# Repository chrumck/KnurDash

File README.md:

# KnurDash - Racing Data Logger with [RaceChrono](https://racechrono.com/) Integration

## Description

A racing logger for an ND2 Mazda MX-5, integrating wide ranging functionality into one unit:

- Reading analog sensors (oil pressure and temperature, rotor temperature)
- Reading CANBUS data (coolant and intake temperature, RPM, etc.)
- Displaying data in a clear and aesthetically pleasing way
- Making data available via Bluetooth as [RaceChrono DIY BLE device](https://github.com/aollin/racechrono-ble-diy-device)

---

## Technical Details

The system has two main components, the display unit and the sensor unit. The communication between the two is executed through I2C protocol (1.2m cable is pushing it though. With careful cable prep I still get ~0.5% error rate on comms.). The display unit is made of a Raspberry Pi 4B board and a [4.3 inch touchscreen](https://www.waveshare.com/4.3inch-dsi-lcd-with-case.htm). The sensor unit houses a [5V power supply](https://www.pololu.com/product/3782/specs), two [4-channel ADC's](https://www.dfrobot.com/index.php?route=product/product&product_id=1182&search=DFR0316), a [motion tracking device](https://www.dfrobot.com/index.php?route=product/product&product_id=880), and a [Longan Labs I2C CAN Controller](https://docs.longan-labs.cc/1030017/) with a [custom firmware](https://github.com/chrumck/I2C_CAN_Firmware) built specifically for this project.

Additionally, the sensor unit contains circuitry [(LTSpice schematic)](./LTSpice/PowerOffCircuit.asc) allowing starting the system when the vehicle's START button is pressed. This has been accomplished by pulling RPI's GLOBAL_EN to ground when RPI is off. When RPI is running and [3.3V is on](https://www.raspberrypi.com/documentation/computers/raspberry-pi.html#POWER_OFF_ON_HALT), the starting circuit is disabled to prevent hard resets while RPI system and the OS is running.

Bluetooth communication was implemented using the [bluez_inc](https://github.com/weliem/bluez_inc) library (kudos to [weliem](https://github.com/weliem) for making my life easier!). The system implements the [RaceChrono BLE DIY](https://github.com/aollin/racechrono-ble-diy-device) protocol. The system works as a pass-through for selected CAN frames. Additionally, all analog data collected by the unit is exposed as an additional CAN frame and made available to RaceChrono for logging.

The display unit has a buzzer installed. The buzzer is turned on when the oil pressure drops below a certain threshold and the RPM is above idling.

The rotor temperature is measured with an industrial grade 0~1000 degC infrared pyrometer with a 4-20mA output.

As of 2023-09-04, the system is installed in the car and in initial testing . The transmission, differential, and rotor temperature sensors were not installed yet, but coming soon!

Future development:

- Read motion tracking data from the already installed unit and expose it to RaceChrono
- Add a [differential GPS](https://www.sparkfun.com/products/15136) board

---

## Pictures

### Display Unit

### Sensor Unit

### Sensors

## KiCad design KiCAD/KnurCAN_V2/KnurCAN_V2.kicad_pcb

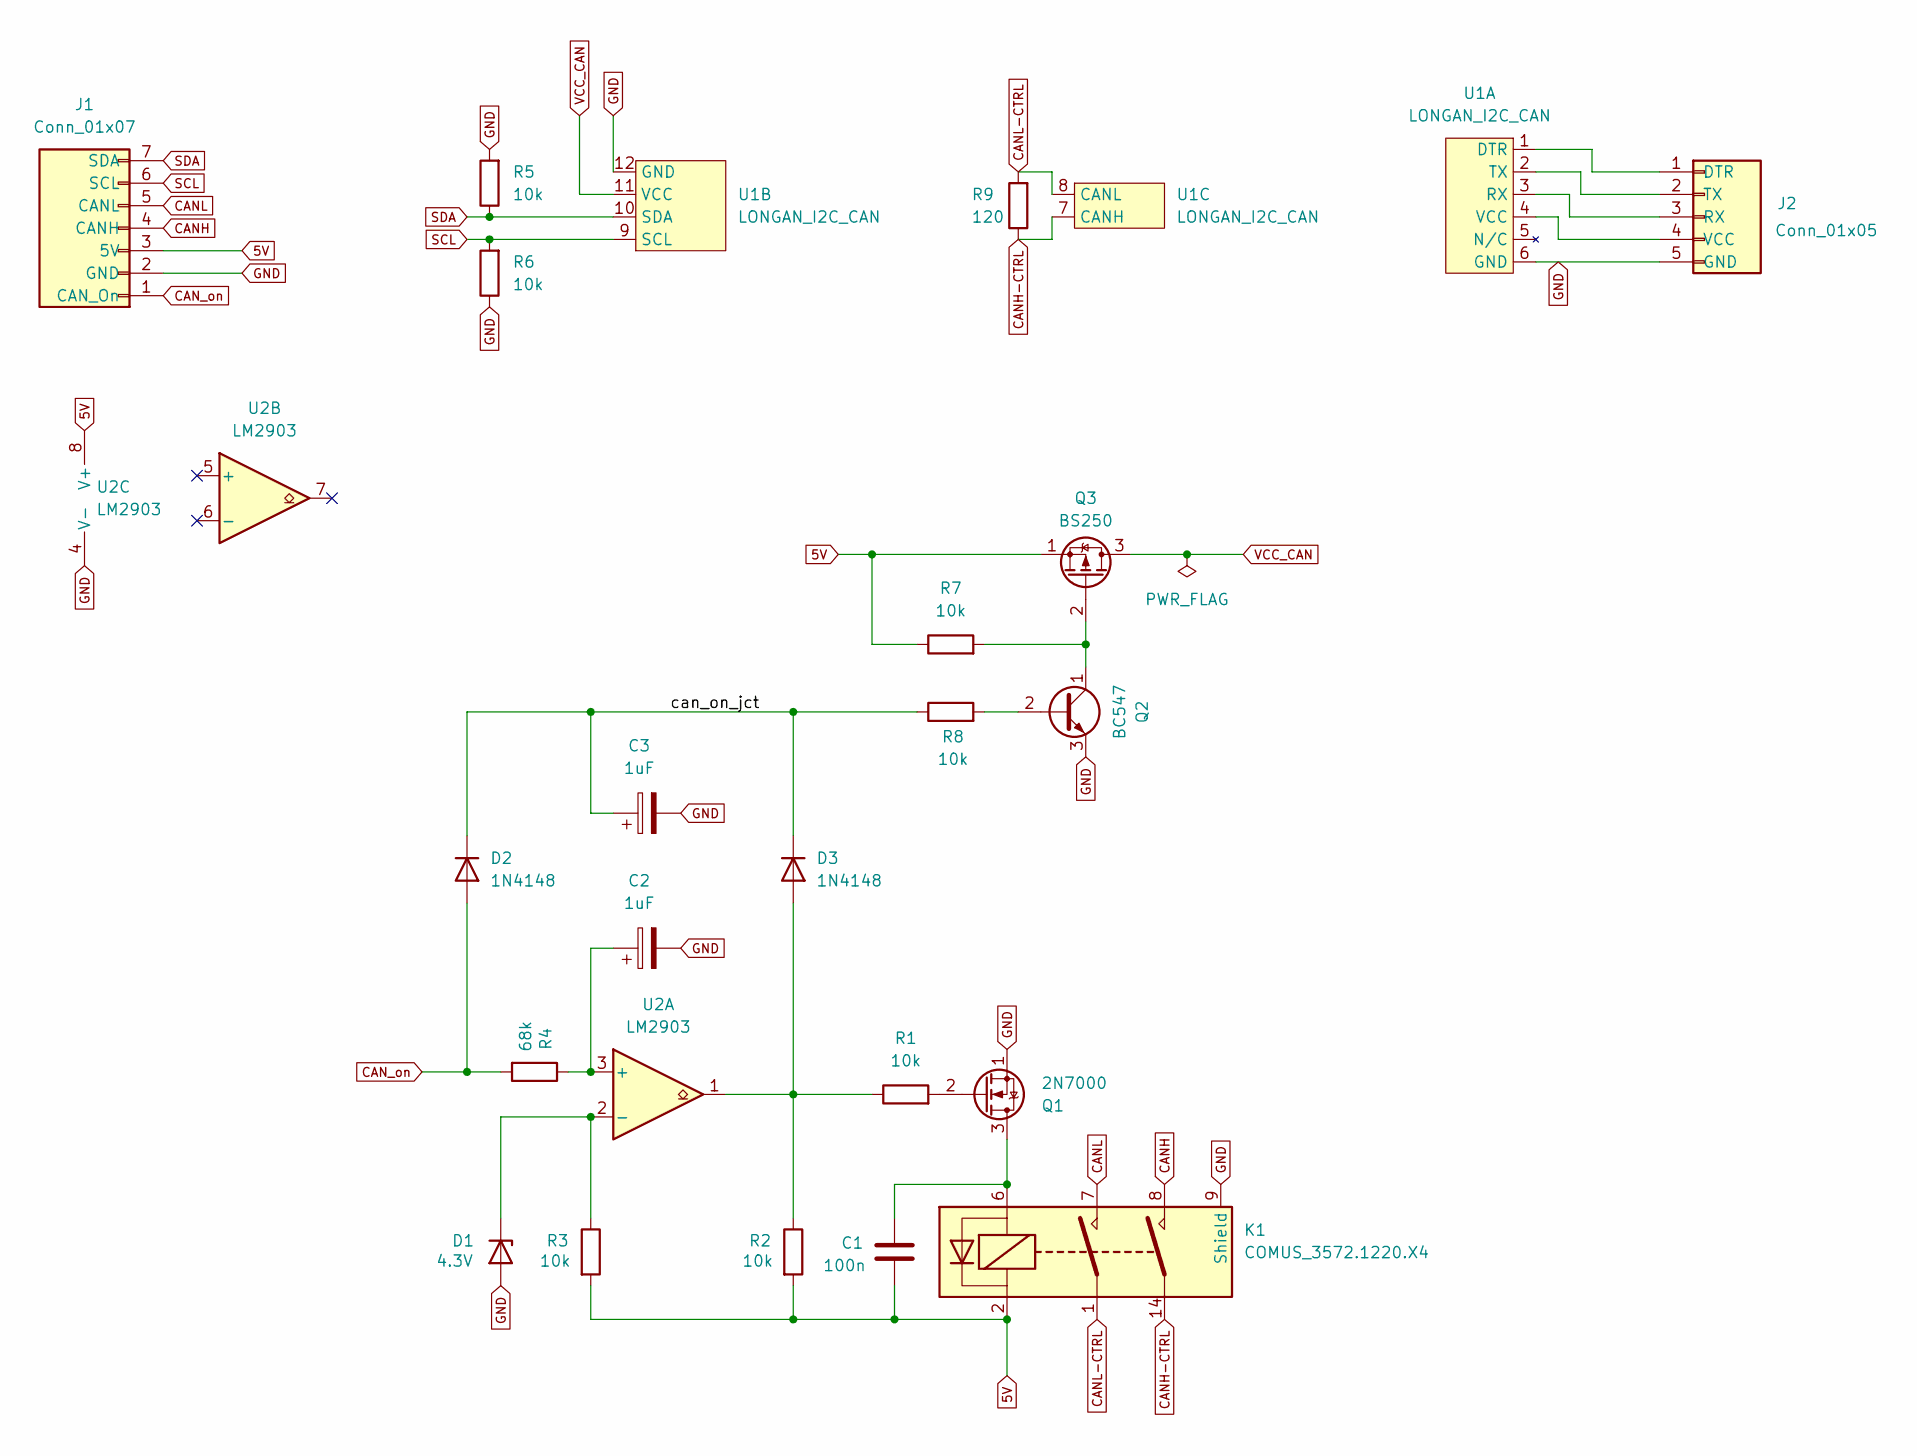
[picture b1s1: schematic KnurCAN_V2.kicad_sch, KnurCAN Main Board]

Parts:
C1: 100n; C_Disc_D3.8mm_W2.6mm_P2.50mm
C2, C3: 1uF; CP_Radial_D5.0mm_P2.50mm
D1: 4.3V; D_DO-35_SOD27_P7.62mm_Horizontal
D2, D3: 1N4148; D_DO-35_SOD27_P7.62mm_Horizontal
J1: Conn_01x07; SolderWire-1x07-d1.5
J2: Conn_01x05; PinHeader_1x05_P2.54mm_Vertical
K1: COMUS_3572.1220.X4; Relay_COMUS_DIP
Q1: 2N7000; TO-92_Inline_Wide
Q2: BC547; TO-92_Inline_Wide
Q3: BS250; TO-92_Inline_Wide
R1, R2, R3, R5, R6, R7, R8: 10k; R_Axial_DIN0207_L6.3mm_D2.5mm_P7.62mm_Horizontal
R4: 68k; R_Axial_DIN0207_L6.3mm_D2.5mm_P7.62mm_Horizontal
R9: 120; R_Axial_DIN0207_L6.3mm_D2.5mm_P7.62mm_Horizontal
U1: LONGAN_I2C_CAN; Longan_I2C_CAN
U2: LM2903; DIP-8_W7.62mm

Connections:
5V: C1.2, J1.3 (5V), K1.2, Q3.1 (S), R2.2, R3.2, R7.1, U2.8 (V+)
/can_on_jct: C3.1, D2.1 (K), D3.1 (K), R8.1
CANH: J1.4 (CANH), K1.8
CANH-CTRL: K1.14, R9.1, U1.7 (CANH)
CANL: J1.5 (CANL), K1.7
CANL-CTRL: K1.1, R9.2, U1.8 (CANL)
CAN_on: D2.2 (A), J1.1 (CAN_On), R4.2
GND: C2.2, C3.2, D1.2 (A), J1.2 (GND), J2.5 (GND), K1.9 (Shield), Q1.1 (S), Q2.3 (E), R5.2, R6.1, U1.6 (GND), U1.12 (GND), U2.4 (V-)
unnamed: D1.1 (K), R3.1, U2.2 (-)
unnamed: D3.2 (A), R1.1, R2.1, U2.1
unnamed: J2.1 (DTR), U1.1 (DTR)
unnamed: J2.3 (RX), U1.3 (RX)
unnamed: J2.2 (TX), U1.2 (TX)
unnamed: J2.4 (VCC), U1.4 (VCC)
unnamed: C1.1, K1.6, Q1.3 (D)
unnamed: Q1.2 (G), R1.2
unnamed: Q2.2 (B), R8.2
unnamed: Q2.1 (C), Q3.2 (G), R7.2
unnamed: C2.1, R4.1, U2.3 (+)
SCL: J1.6 (SCL), R6.2, U1.9 (SCL)
SDA: J1.7 (SDA), R5.1, U1.10 (SDA)
VCC_CAN: Q3.3 (D), U1.11 (VCC)

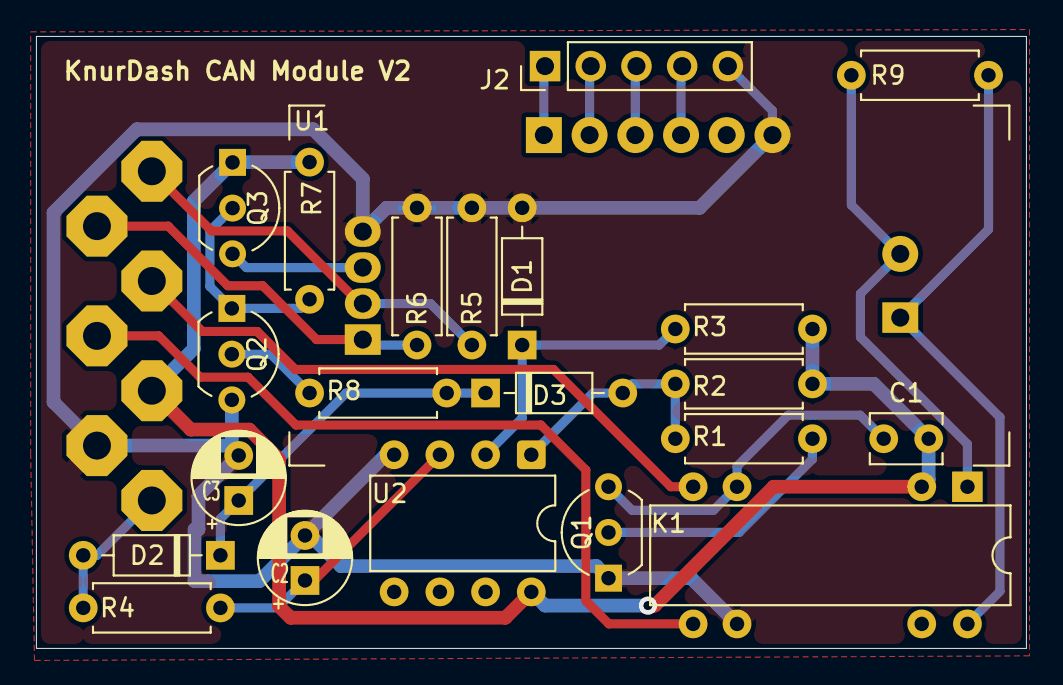
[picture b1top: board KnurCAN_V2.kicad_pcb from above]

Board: 2 copper layers, 55.0 x 34.0 mm, 23 parts (0 on the bottom side), 22 nets.

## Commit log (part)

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2023-05-14 Add gtk3
2023-05-14 Update gitignore
2023-05-14 Clean up CMakeLists, add main.ui
2023-05-14 Minor updates
2023-05-14 More fixes
2023-05-15 Tinkering with main.ui parsing
2023-05-15 Added TURN OFF button
2023-05-15 Fix uiFileName weird bug - strange characters
2023-05-15 Add width and height to KnurDash.ui
2023-05-15 Remove compiled files
2023-05-15 Set decorate false and go fullscreen
2023-05-16 Add CSS, finish ui work
2023-05-17 Add setBrightness
2023-05-19 remove Print_hello
2023-05-19 Put brightness logic in separate file
2023-05-19 Add sensors.c
2023-05-19 trying to fix language mode incompatible
2023-05-20 First try to add pigpio
2023-05-20 second attempt to link pigpio
2023-05-20 Refactor shutDown to gracefully stop workers
2023-05-20 Add buttonShutDown and windowShutDown
2023-05-20 Change code to use pigpiod deamon
2023-05-20 Move shutdown callbacks to ui.c
2023-05-20 Add i2cOpen
2023-05-20 2st try to read from adc
2023-05-20 Change to i2c_read_device; maybe fix cmake extension problems
2023-05-20 Getting first readings from channel 1
2023-05-20 Minor cleanup and progress
2023-05-21 Clean up filepath stuff
2023-05-21 minor fix
2023-05-21 Add deadband
2023-05-21 Finish reading oil channel, I wonder if it works
2023-05-22 Refactor ReadChannelArgs into ChannelProps
2023-05-22 Refactor sensors.c to take new SensorProps
2023-05-22 Start working on populating min/max values
2023-05-23 Renames and cleanup
2023-05-23 More minor fixes and cleanup
2023-05-23 Add resetting min and max. Other refactor and cleanup
2023-05-23 Fix memory leak around SetLabelArgs
2023-05-23 convert some macros to functions
2023-05-24 Fix bug with min max labels not available for min max reset; Cleanup and refactor
2023-05-24 Add precision and deadband logic
2023-05-24 Add testing limits and handling css classes
2023-05-24 Minor tweak to css
2023-05-24 Add FAULTY_READING_VALUE
2023-05-24 Minor fix in resetLastReadings
2023-05-25 Add VDD sensor reading and consume it for other sensors
2023-05-25 update compile files
2023-05-28 Add reading ignition state and shutdown on ignition off
2023-05-28 Build release
2023-05-29 Add design files and photos
2023-05-29 update xls
2023-05-30 update pics
2023-06-03 Tweak sensor props
2023-06-03 update build files
2023-06-11 Minor cleanup
2023-06-11 Minor refactor
2023-06-11 Add handling of unix signals
2023-06-11 Minor update
2023-06-11 Add boot folder
2023-06-12 Add bluez_inc
2023-06-12 Reconfigure CMakeLists to include Binc
2023-06-15 Add bluetoothWorker.c
2023-06-16 Add attempt to power back up if bt adapter not powered
2023-06-16 Progressing work on bt worker
2023-06-16 Continuing work with bt worker
2023-06-17 Add CAN decoding xls
2023-06-18 Finished BT worker shutdown logic
2023-06-18 disable app shutdown on engine off when debugging
2023-07-11 Add dbc for SavvyCAN
2023-07-11 Update x202 frame defs
2023-07-11 More work on DBC
2023-07-11 xlsx update
2023-07-12 Update log messages and shutdown logic
2023-07-12 update knurdash.service with TimeoutStopSec=5
2023-07-12 Move initializing pigpiod pi handle to main.c
2023-07-12 Add CanBusData DTO
2023-07-13 Add canBusWorker
2023-07-13 update write result check
2023-07-13 Add mask and filter setting
2023-07-13 Add can filter/mask messaging and delay in setting
2023-07-14 Add 3 more frame ids
2023-07-15 Add early return to CAN setMaskOrFilter
2023-07-15 Add canBusProps file; move constants there; start working on storing can frames
2023-07-15 Move worker data to a global variable
2023-07-15 Fix bt worker not shutting down properly
2023-07-15 Start adding canbus worker loops
2023-07-15 change isSent to isReady
2023-07-15 add sensors frame id
2023-07-16 Rename to KNURDASH_FRAME_ID
2023-07-16 Add workerData.c to canBusWorker
2023-07-16 add getFrameFromCAN
2023-07-16 Add getRpm
2023-07-16 Add buzzer handling to sensorWorker
2023-07-16 minor fixes
2023-07-17 Add IS_DEBUG
2023-07-17 leave buzzer logic on when debugging
2023-07-17 update CAN errors reporting
2023-07-17 fix bug in setMaskOrFilter - delete extra return;
2023-07-17 Make canbus statistics be reported at shutdown
2023-07-18 minor messages formatting
2023-07-18 Refactor gauges to consolidate min/max with main label
2023-07-18 Update css to match the new UI
2023-07-18 Rename windowShutdown to appShutdown
2023-07-18 refactor shutDown to accept ShutdownType enum as pointer
2023-07-18 minor rename
2023-07-19 Refactor sensor DTO to separate base properties
2023-07-19 Add CanSensor DTO and definition for coolant temp
2023-07-19 Add coolant temp can sensor to sensorWorker
2023-07-19 Add request rejected check in setMaskOfFilter
2023-07-19 decrease can buss polling to ~20Hz
2023-07-19 update error messages
2023-07-19 update temp sensors min/max values
2023-07-19 bump OIL_PRESSURE_ALERT_MIN_RPM
2023-07-19 minor cleanup in ui
2023-07-19 add ENABLE_CAN_READ_ERROR_LOGGING
2023-07-20 Add btWasSent reset to getFrameFromCAN
2023-07-20 move bt advertisement to workerData
2023-07-20 wire up onCharStartNotify and onCharStopNotify
2023-07-20 Set BT error messages
2023-07-22 add reading locking on reading update; clean up reading sensor logic
2023-07-22 start adding getAdcFrame
2023-07-22 add racechrono to workspace dict
2023-07-22 finish implementation of getAdcFrame
2023-07-22 fix typo in getAdcFrame
2023-07-22 add sensor reading locking in resetReadingsValues
2023-07-22 read adc sensors in reverse order
2023-07-22 fix getAdc frame passing
2023-07-23 make sensorWorker set adc can frame
2023-07-23 move CAN_FRAME_ID_LENGTH to dataContracts
2023-07-23 lock adc can frame before setting default values
2023-07-23 implement onCharRead
2023-07-23 rename sensorData to sensors
2023-07-23 rename canBusData to canBus
2023-07-23 rename bluetoothData to bluetooth
2023-07-23 Start implementing onCharWrite
2023-07-23 add early return on requestShutdown in getFrameFromCAN
2023-07-23 add sendCanFrameToBt, continue with onCharWrite
2023-07-23 finish implementation onCharWrite
2023-07-23 update bt logging
2023-07-23 fix bug aroung byte array sizing
2023-07-23 round temps to nearest degree before creating adc can frame
2023-07-23 increase data acquisition speed
2023-07-23 tweak bt and canbus shutdown logic
2023-07-24 make sure the min,max are repopulated after clearing
2023-07-24 add error rate tracking to sensor readings
2023-07-24 Add bluetooth.isConnected and removing sources on disconnecting
2023-07-24 Add app shutdown on excessive canbus error rate
2023-07-24 fix bug in getting connection state name
2023-07-24 fix source removing logic in bluetooth worker
2023-07-24 switch to release version
2023-07-24 remove bluetooth.isConnected
2023-07-24 set bt worker log level to info at all times
2023-07-24 add disconnecting info on shutdown
2023-07-25 update dbc
2023-07-25 fix pressure rounding bug
2023-07-25 clean up buzzer on/off logic
2023-08-29 update dbc file
2023-08-29 canbus decoding updates
2023-08-30 working on CAN decoding
2023-08-31 Add rotor temp sensor definition
2023-08-31 updates to sensor calcs
2023-09-02 Update pinouts
2023-09-02 add adcConfig to AdcSensor definition
2023-09-02 Add rotor temp reading step to sensor worker; change temp offset to 40degC
2023-09-02 Change MAX_REQUEST_ERROR_RATE to 0.20
2023-09-02 Add rotor temp to ui
2023-09-02 Fix rotor temp calcs
2023-09-03 Add startup retry logic to canBusWorker
2023-09-03 add 5 second delay to shutting down due to errors
2023-09-04 update bluez_inc to latest master
2023-09-04 Update photos and add README
2023-09-04 Add license
2023-09-10 can decoding updates
2023-09-10 update coolant temp rawMin and rawMax
2023-09-10 add delay between canbus start retries
2023-09-10 bump pressure precision to 0.05 bar
2023-09-11 add diff and trans temp frames to ui
2023-09-11 update wiring file
2023-09-12 add fault tolerance of 5 faults to sensorworker
2023-09-12 allow more sensor worker logging when error count > 5
2023-09-13 Add more shutdown scenarios
2023-09-13 change canbus frame state from receiveFailed to errorCount
2023-09-13 add repeat reading of mask/filter after setting it.
2023-09-13 improve sensor worker shutdown logic when CAN coolant temp reading in error
2023-09-13 Improve messaging for CAN initialization
2023-09-13 Do not increment sensors.errorCount on repeat out of range readings
2023-09-14 Add checksum to mask/filter setting
2023-09-14 fix mask/filter getting logic - request to get and response too fast
2023-09-14 tweak shutting down on coolant errors
2023-09-14 bump request error rate to 0.5
2023-09-14 minor tweak to shutting down on coolant errors
2023-09-18 add CAN controller switch on/off to canBusWorker
2023-09-18 improve can error handling in sensorWorker
2023-09-19 fix flickering can sensor on ignition off
2023-09-19 Add CAN restart logic without restarting the app
2023-09-19 fix bug in restartCanBus
2023-12-19 Rename WorkerData to AppData
2023-12-19 Add volatile keyword to AppData
2024-02-25 update xls file
2024-02-29 update binc ref to latest main
2024-02-29 remove volatile from appData
2024-02-29 updae build json
2024-03-04 Add ENABLE_CANBUS
2024-03-05 bum CAN I2C request delay to 2ms
2024-03-06 move adc bit resolution to #define
2024-03-06 horten sensorWorker idle time to 25m
2024-03-08 minor refactor and renames
2024-03-08 remove sensorWorker wait on canBusWorker; other minor refactor
2024-03-08 refactor AdcSensor to have pga; no support for adaptive pgs yet; add def for caliper temp
2024-03-08 add support for adaptive pga
2024-03-09 fixes to ui
2024-03-09 fix sensorWorker usage of readAdc
2024-03-09 finish sensor definition for caliper temp
2024-03-09 enable caliper temp reading in sensorWorker
2024-03-09 make canBusWorker abort CAN init on appShutdownRequested
2024-03-09 add config.txt to boot folder
2024-03-09 make sure sensorWorker does not read can sensors if canbus not started
2024-03-09 bump CANBUS startup times
2024-03-09 bump i2c request delay to 3000 us
2024-03-09 revert back to 2ms for canbus i2c request delay
2024-03-10 increase wait time after request for filter, mask
2024-03-10 increase wait time before CAN restart request
2024-03-10 change the way context_iteration is invoked
2024-03-10 change usage of context_iteration in btWorker
2024-03-10 remove pin setting from config.txt
2024-03-10 move can switchoff logic to stopCanBusWorker
2024-03-10 remove i2c_read_byte_data
2024-03-10 lower wait time before restarting canbus from sensorworker
2024-03-10 lower canbus wait times
2024-03-10 update build #
2024-03-10 update build index
2024-03-13 bump lower rotor temp limit to 50 degC
2024-03-13 update build json
2024-03-13 update SensorUnit xls
2024-03-29 tweak rotor temp and oil pressure limits
2024-04-30 updates to SensorUnit; design for trans pump
2024-05-02 Split code from sensorWorker to systemWorker
2024-05-02 Add trans pump switching logic
2024-05-02 Update ui for trans cooling info
2024-05-03 css fixes; add systemWorker to main
2024-05-03 reduce number of status gauges to 2; other ui tweaks
2024-05-03 fix css for status gagues
2024-05-03 add trans pump ui status toggling to system worker
2024-05-03 add sensor worker started message
2024-05-05 change trans pump GPIO to high for ON
2024-05-05 update to CANBUS start, make it wait for sensorWorker
2024-05-05 fix trans pump shutdown at app shutdown
2024-05-05 set trans pump on temp to 95 c
2024-05-05 add isSystemWorkerRunning
2024-07-14 set trans pump off temp to 50 degC
2024-07-23 add app_error; take advantage of pragma once
2024-07-23 adjust temperature limits
2024-07-24 refactor logging and graceful shutdown
2024-07-24 add buzzerToggleTimestamp; more cleanup
2024-07-26 tweak limit values; other refactor
2024-07-26 Add buzzer chirping
2024-07-26 tweak buzzer chirp logic to use cycles instead of us
2024-07-26 minor tweak in chirp logic
2024-07-26 update buzzer logic so it does not run when ign off and rpm below threshold
2025-06-21 Add PCB design for KnurCAN_V2
2025-06-21 update gitignore to exclude kicad backups
2025-08-16 design file updates
2025-08-16 update canBusWorker to work with KnurCan V2
2025-08-16 update bluez_inc to latest main
2025-09-07 Add IAT to screen
2025-09-07 add missing readCanSensor call for IAT
